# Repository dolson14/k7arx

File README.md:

# K7ARX Project Repository

A place to keep research and work on various electronics and radio projects.

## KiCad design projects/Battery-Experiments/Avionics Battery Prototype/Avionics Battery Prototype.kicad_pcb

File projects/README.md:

# Projects

Hardware, software, vaporware!

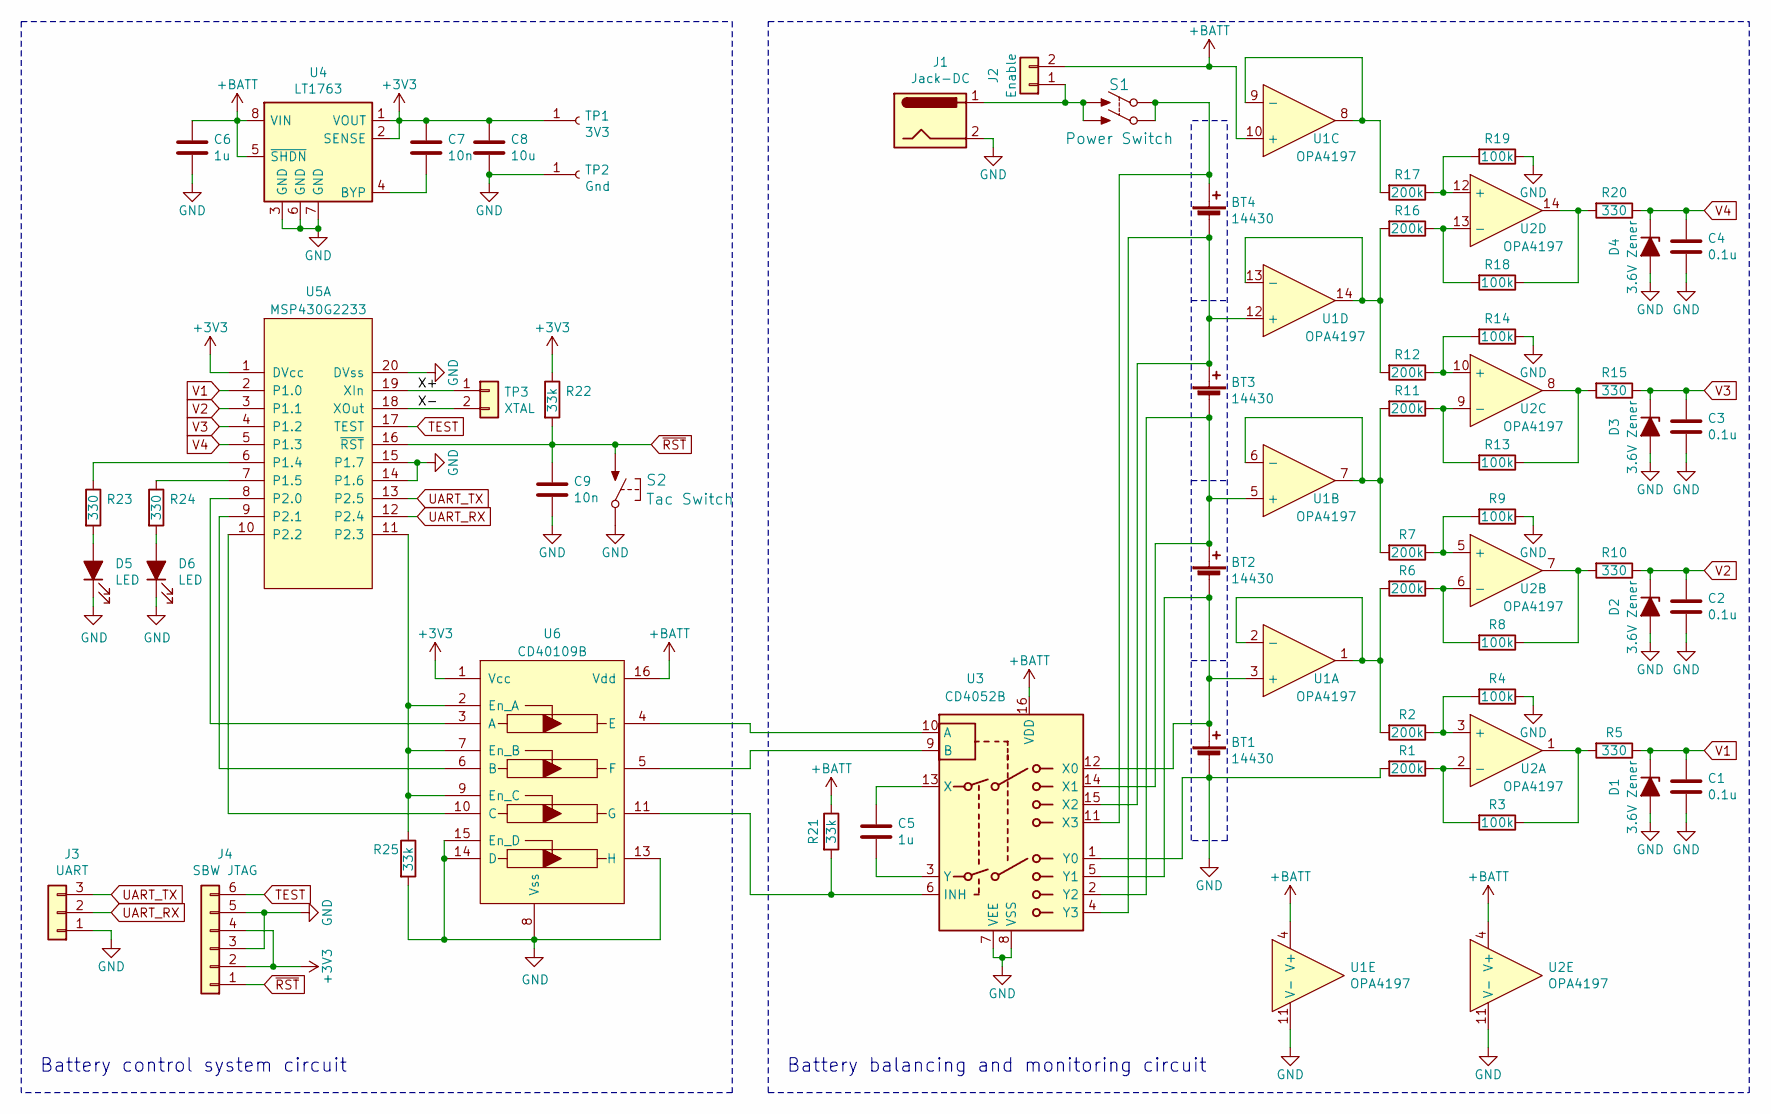
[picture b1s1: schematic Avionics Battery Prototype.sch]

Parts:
BT1, BT2, BT3, BT4: 14430; Keystone-92 Battery_Contact 14430
C1, C2, C3, C4: 0.1u; C_1206_HandSoldering
C5, C6: 1u; C_1206_HandSoldering
C7, C9: 10n; C_1206_HandSoldering
C8: 10u; C_1206_HandSoldering
D1, D2, D3, D4: 3.6V Zener; D_SOD-123F
D5, D6: LED; LED_1206_HandSoldering
J1: Jack-DC; Banana_Jack_2Pin
J2: Enable; Pin_Header_Straight_1x02_Pitch2.54mm
J3: UART; Pin_Header_Straight_1x03_Pitch2.54mm
J4: SBW JTAG; Tag-Connect_TC2030-NL
R1, R2, R6, R7, R11, R12, R16, R17: 200k; R_1206_HandSoldering
R3, R4, R8, R9, R13, R14, R18, R19: 100k; R_1206_HandSoldering
R5, R10, R15, R20, R23, R24: 330; R_1206_HandSoldering
R21, R22, R25: 33k; R_1206_HandSoldering
S1: Power Switch; PB400 DPST Pushbutton Switch
S2: Tac Switch; EVQ2_Momentary_Switch
TP1: 3V3; Pin_Header_Straight_1x01_Pitch2.54mm
TP2: Gnd; Pin_Header_Straight_1x01_Pitch2.54mm
TP3: XTAL; 8MM-11 2-pin PCB socket
U1, U2: OPA4197; SOIC-14_N
U3: CD4052B; SO-16-N
U4: LT1763; SOIC-8-N
U5: MSP430G2233; SSOP-20
U6: CD40109B; SO-16-N

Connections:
+3V3: C7.1, C8.1, J4.2, J4.4, R22.1, TP1.1, U4.1 (VOUT), U4.2 (SENSE), U5.1 (DVcc), U6.1 (Vcc)
+BATT: C6.1, J2.2, R21.1, U1.4 (V+), U1.10 (+), U2.4 (V+), U3.16 (VDD), U4.5 (~SHDN), U4.8 (VIN), U6.16 (Vdd)
/X+: TP3.1, U5.19 (XIn)
/X-: TP3.2, U5.18 (XOut)
GND: BT1.2 (-), C1.2, C2.2, C3.2, C4.2, C6.2, C8.2, C9.2, D1.2 (A), D2.2 (A), D3.2 (A), D4.2 (A), D5.1 (K), D6.1 (K), J1.2, J3.1, J4.3, J4.5, R1.2, R4.1, R9.1, R14.1, R19.1, R25.2, S2.2 (COM), TP2.1, U1.11 (V-), U2.11 (V-), U3.1 (Y0), U3.7 (VEE), U3.8 (VSS), U4.3 (GND), U4.6 (GND), U4.7 (GND), U5.14 (P1.6), U5.15 (P1.7), U5.20 (DVss), U6.8 (Vss), U6.13 (H), U6.14 (D), U6.15 (En_D)
unnamed: BT1.1 (+), BT2.2 (-), U1.3 (+), U3.5 (Y1), U3.12 (X0)
unnamed: BT2.1 (+), BT3.2 (-), U1.5 (+), U3.2 (Y2), U3.14 (X1)
unnamed: BT3.1 (+), BT4.2 (-), U1.12 (+), U3.4 (Y3), U3.15 (X2)
unnamed: BT4.1 (+), S1.2 (COM1), S1.4 (COM2), U3.11 (X3)
unnamed: C5.1, U3.13 (X)
unnamed: C5.2, U3.3 (Y)
unnamed: C7.2, U4.4 (BYP)
unnamed: D5.2 (A), R23.2
unnamed: D6.2 (A), R24.2
unnamed: J1.1, J2.1, S1.1 (NO1), S1.3 (NO2)
unnamed: R1.1, R3.2, U2.2 (-)
unnamed: R2.1, R4.2, U2.3 (+)
unnamed: R2.2, R6.2, U1.1, U1.2 (-)
unnamed: R3.1, R5.2, U2.1
unnamed: R6.1, R8.2, U2.6 (-)
unnamed: R7.1, R9.2, U2.5 (+)
unnamed: R8.1, R10.2, U2.7
unnamed: R11.1, R13.2, U2.9 (-)
unnamed: R7.2, R11.2, U1.6 (-), U1.7
unnamed: R12.1, R14.2, U2.10 (+)
unnamed: R12.2, R16.2, U1.13 (-), U1.14
unnamed: R13.1, R15.2, U2.8
unnamed: R16.1, R18.2, U2.13 (-)
unnamed: R17.1, R19.2, U2.12 (+)
unnamed: R17.2, U1.8, U1.9 (-)
unnamed: R18.1, R20.2, U2.14
unnamed: R21.2, U3.6 (INH), U6.11 (G)
unnamed: R23.1, U5.6 (P1.4)
unnamed: R24.1, U5.7 (P1.5)
unnamed: R25.1, U5.11 (P2.3), U6.2 (En_A), U6.7 (En_B), U6.9 (En_C)
unnamed: U3.9 (B), U6.5 (F)
unnamed: U3.10 (A), U6.4 (E)
unnamed: U5.8 (P2.0), U6.3 (A)
unnamed: U5.9 (P2.1), U6.6 (B)
unnamed: U5.10 (P2.2), U6.10 (C)
TEST: J4.6, U5.17 (TEST)
UART_RX: J3.2, U5.12 (P2.4)
UART_TX: J3.3, U5.13 (P2.5)
V1: C1.1, D1.1 (K), R5.1, U5.2 (P1.0)
V2: C2.1, D2.1 (K), R10.1, U5.3 (P1.1)
V3: C3.1, D3.1 (K), R15.1, U5.4 (P1.2)
V4: C4.1, D4.1 (K), R20.1, U5.5 (P1.3)
~RST: C9.1, J4.1, R22.2, S2.1 (NO), U5.16 (~RST)

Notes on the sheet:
Battery balancing and monitoring circuit
Battery control system circuit

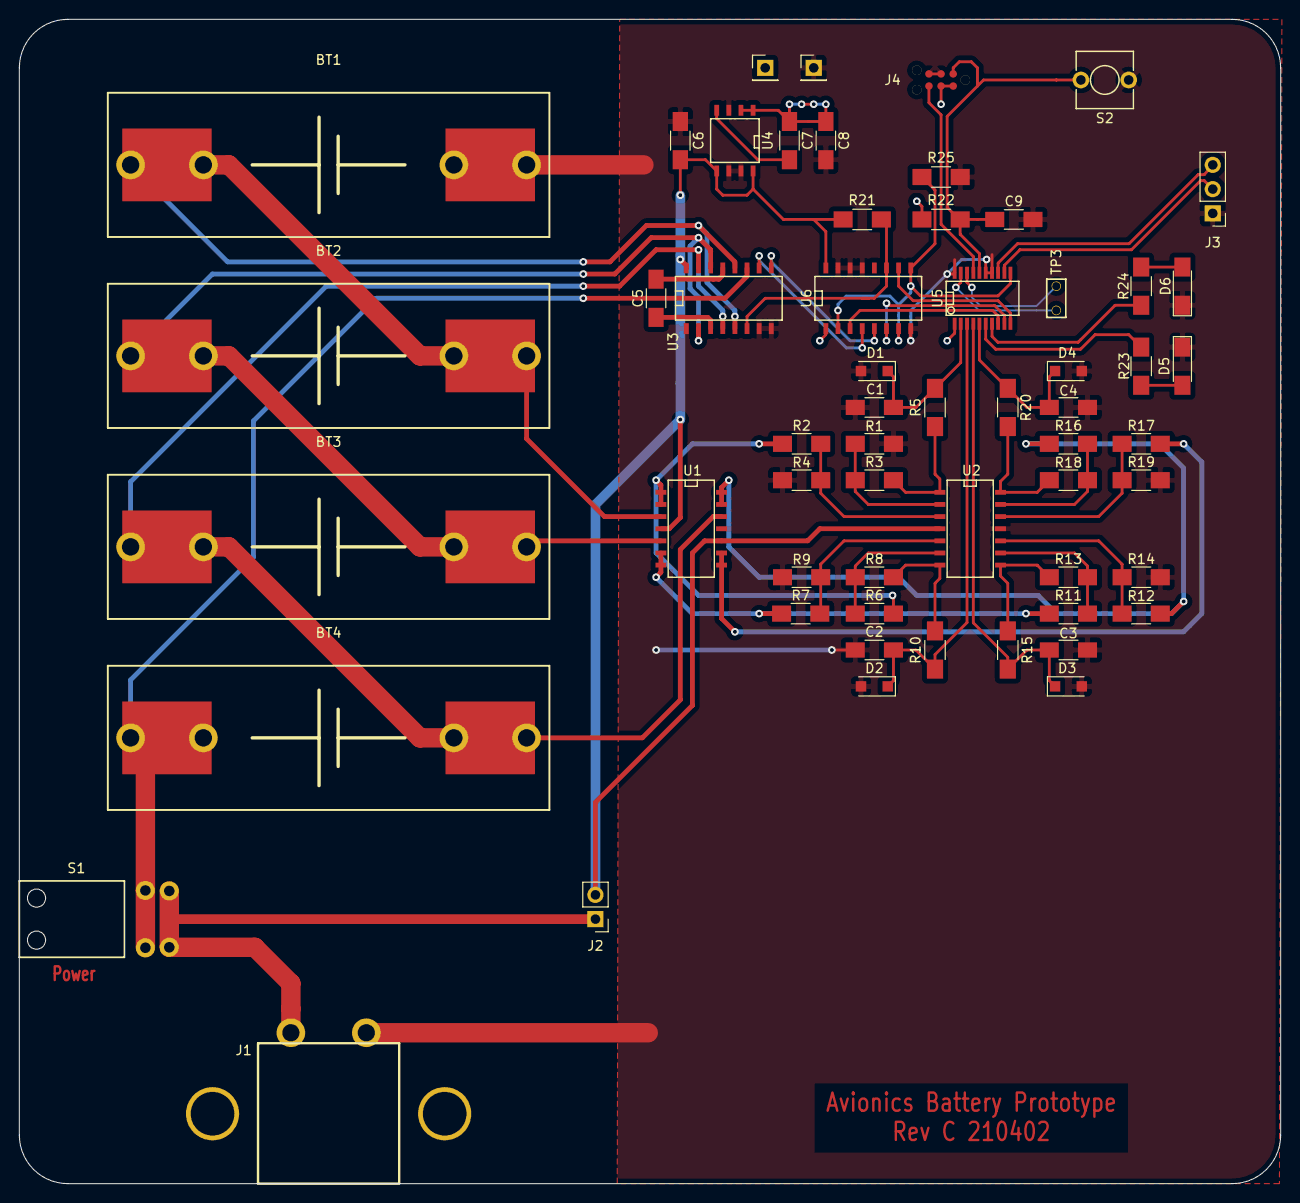
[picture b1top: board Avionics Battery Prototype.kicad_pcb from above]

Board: 2 copper layers, 132.1 x 121.9 mm, 59 parts (0 on the bottom side), 48 nets.

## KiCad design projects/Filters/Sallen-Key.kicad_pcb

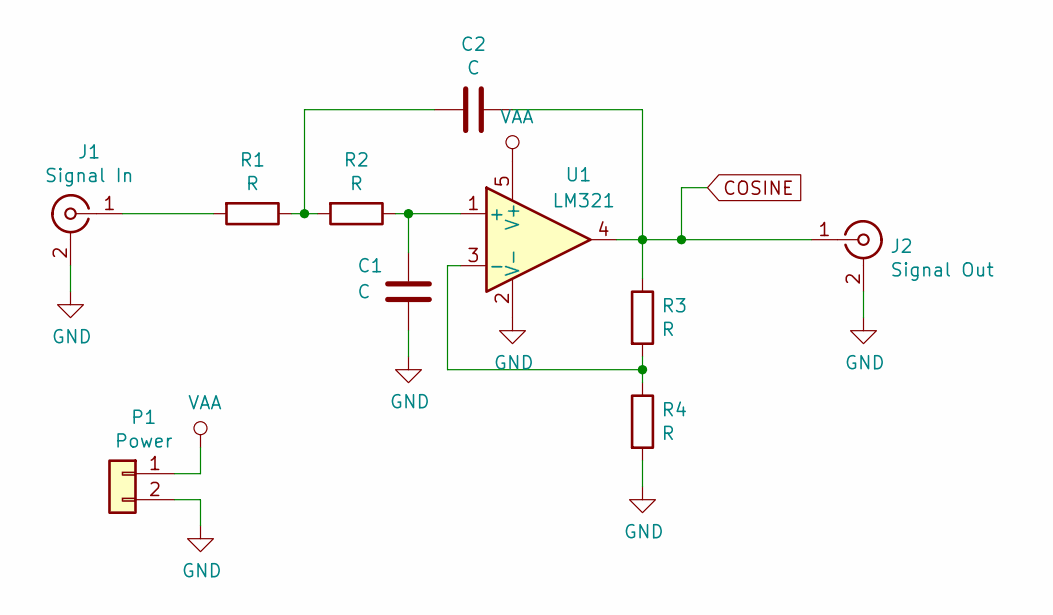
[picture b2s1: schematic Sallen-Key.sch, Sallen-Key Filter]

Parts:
C1, C2: C; C_0805_2012Metric_Pad1.15x1.40mm_HandSolder
J1: Signal In; SMA_Amphenol_132289_EdgeMount
J2: Signal Out; SMA_Amphenol_132289_EdgeMount
P1: Power; EP_3.96-pin_1x2
R1, R2, R3, R4: R; R_0805_2012Metric_Pad1.15x1.40mm_HandSolder
U1: LM321; SOT-23-5

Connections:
COSINE: C2.1, J2.1 (In), R3.1, U1.4
GND: C1.2, J1.2 (Ext), J2.2 (Ext), P1.2, R4.2, U1.2 (V-)
unnamed: C1.1, R2.1, U1.1 (+)
unnamed: C2.2, R1.1, R2.2
unnamed: J1.1 (In), R1.2
unnamed: R3.2, R4.1, U1.3 (-)
VAA: P1.1, U1.5 (V+)

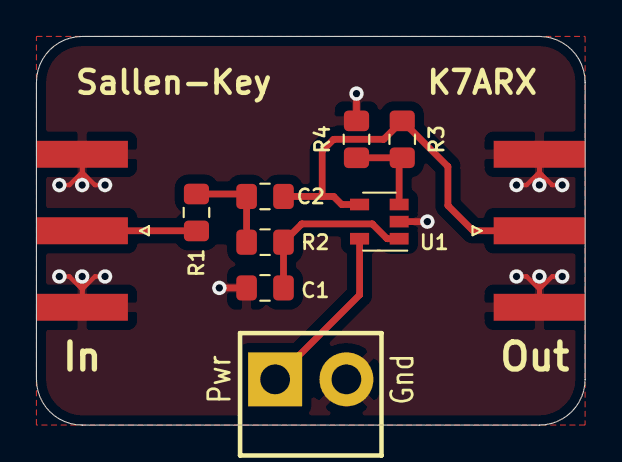
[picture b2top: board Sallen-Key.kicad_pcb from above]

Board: 2 copper layers, 30.5 x 21.6 mm, 10 parts (0 on the bottom side), 7 nets.

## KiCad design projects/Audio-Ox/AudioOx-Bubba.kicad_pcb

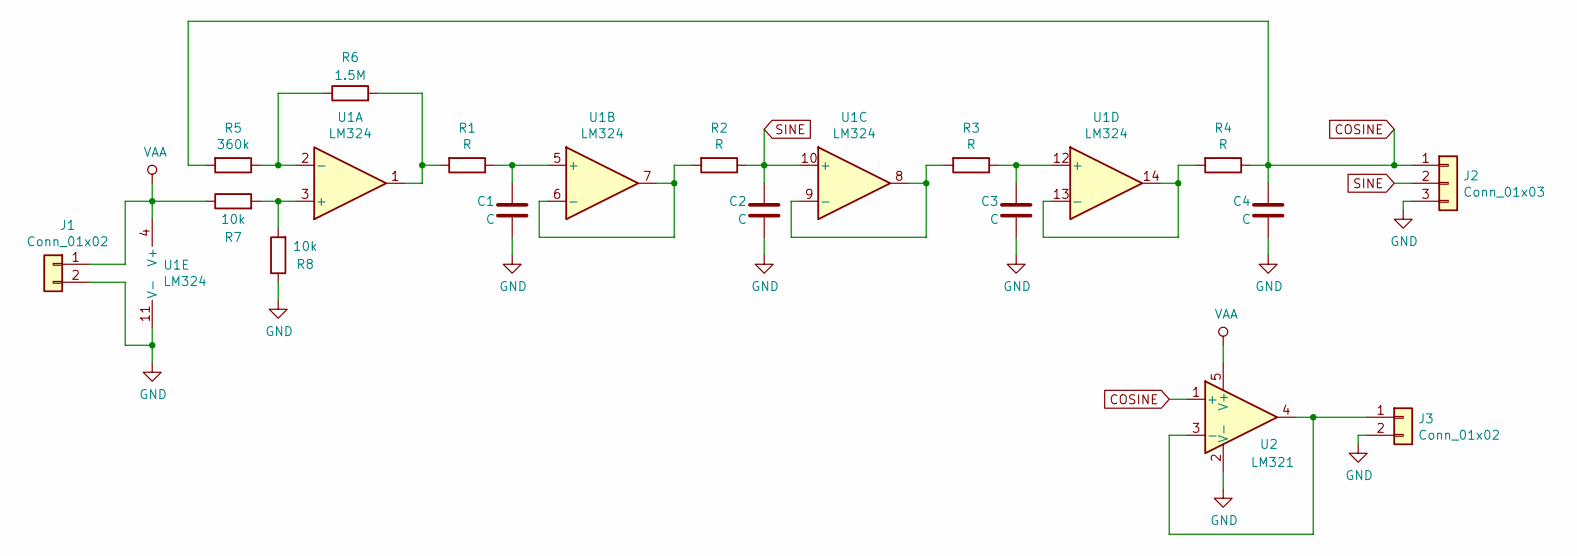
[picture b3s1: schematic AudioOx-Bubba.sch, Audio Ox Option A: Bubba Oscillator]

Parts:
C1, C2, C3, C4: C; C_0805_2012Metric_Pad1.15x1.40mm_HandSolder
J1, J3: Conn_01x02; PinHeader_1x02_P2.54mm_Vertical
J2: Conn_01x03; PinHeader_1x03_P2.54mm_Vertical
R1, R2, R3, R4: R; R_0805_2012Metric_Pad1.15x1.40mm_HandSolder
R5: 360k; R_0805_2012Metric_Pad1.15x1.40mm_HandSolder
R6: 1.5M; R_0805_2012Metric_Pad1.15x1.40mm_HandSolder
R7, R8: 10k; R_0805_2012Metric_Pad1.15x1.40mm_HandSolder
U1: LM324; SOIC-14_3.9x8.7mm_P1.27mm
U2: LM321; SOT-23-5

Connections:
COSINE: C4.1, J2.1, R4.1, R5.2, U2.1 (+)
GND: C1.2, C2.2, C3.2, C4.2, J1.2, J2.3, J3.2, R8.1, U1.11 (V-), U2.2 (V-)
unnamed: C1.1, R1.1, U1.5 (+)
unnamed: C3.1, R3.1, U1.12 (+)
unnamed: J3.1, U2.3 (-), U2.4
unnamed: R1.2, R6.2, U1.1
unnamed: R2.2, U1.6 (-), U1.7
unnamed: R3.2, U1.8, U1.9 (-)
unnamed: R4.2, U1.13 (-), U1.14
unnamed: R5.1, R6.1, U1.2 (-)
unnamed: R7.2, R8.2, U1.3 (+)
SINE: C2.1, J2.2, R2.1, U1.10 (+)
VAA: J1.1, R7.1, U1.4 (V+), U2.5 (V+)

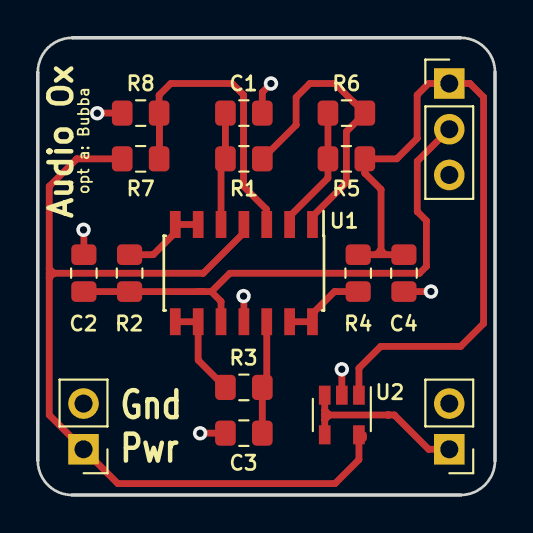
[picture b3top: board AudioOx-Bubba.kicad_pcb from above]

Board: 2 copper layers, 25.4 x 25.4 mm, 17 parts (0 on the bottom side), 13 nets.

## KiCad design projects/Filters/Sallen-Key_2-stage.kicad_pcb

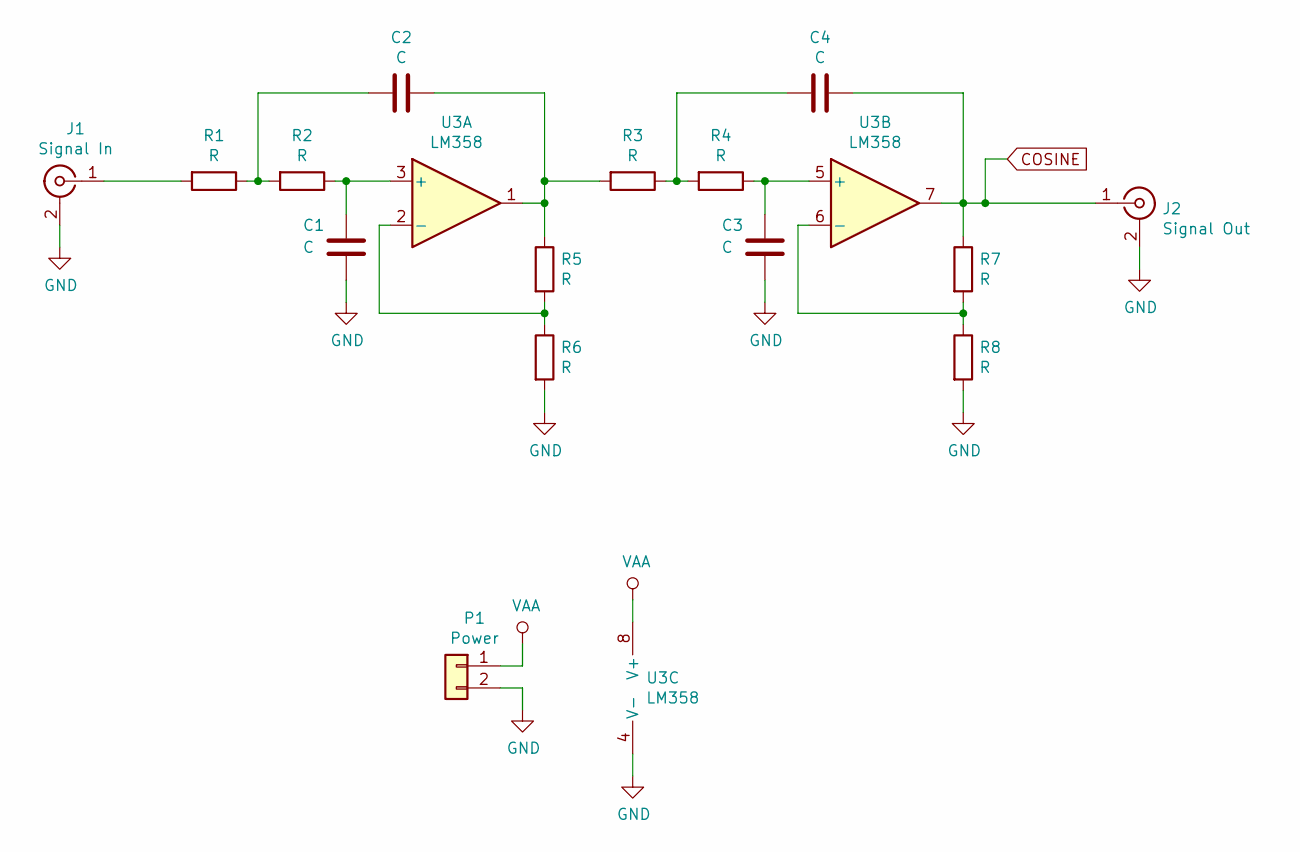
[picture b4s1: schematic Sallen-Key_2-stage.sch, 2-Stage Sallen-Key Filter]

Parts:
C1, C2, C3, C4: C; C_0805_2012Metric_Pad1.15x1.40mm_HandSolder
J1: Signal In; SMA_Amphenol_132289_EdgeMount
J2: Signal Out; SMA_Amphenol_132289_EdgeMount
P1: Power; EP_3.96-pin_1x2
R1, R2, R3, R4, R5, R6, R7, R8: R; R_0805_2012Metric_Pad1.15x1.40mm_HandSolder
U3: LM358; SOIC-8_3.9x4.9mm_P1.27mm

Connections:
COSINE: C4.1, J2.1 (In), R7.1, U3.7
GND: C1.2, C3.2, J1.2 (Ext), J2.2 (Ext), P1.2, R6.2, R8.2, U3.4 (V-)
unnamed: C1.1, R2.1, U3.3 (+)
unnamed: C2.1, R3.2, R5.1, U3.1
unnamed: C2.2, R1.1, R2.2
unnamed: C3.1, R4.1, U3.5 (+)
unnamed: C4.2, R3.1, R4.2
unnamed: J1.1 (In), R1.2
unnamed: R5.2, R6.1, U3.2 (-)
unnamed: R7.2, R8.1, U3.6 (-)
VAA: P1.1, U3.8 (V+)

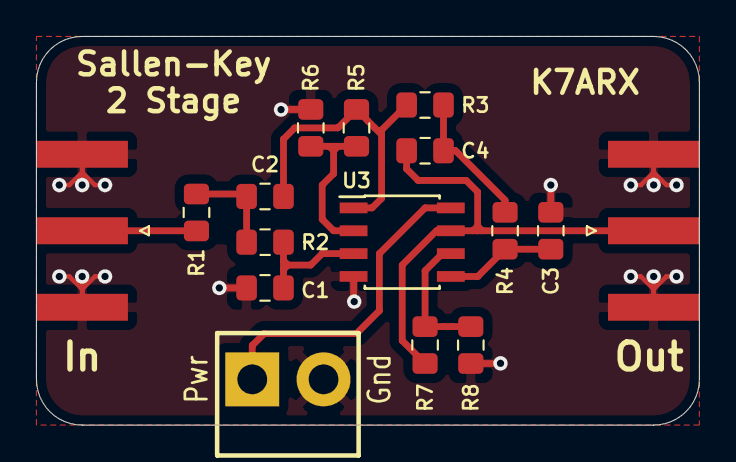
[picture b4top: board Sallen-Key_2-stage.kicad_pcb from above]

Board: 2 copper layers, 36.8 x 21.6 mm, 16 parts (0 on the bottom side), 11 nets.

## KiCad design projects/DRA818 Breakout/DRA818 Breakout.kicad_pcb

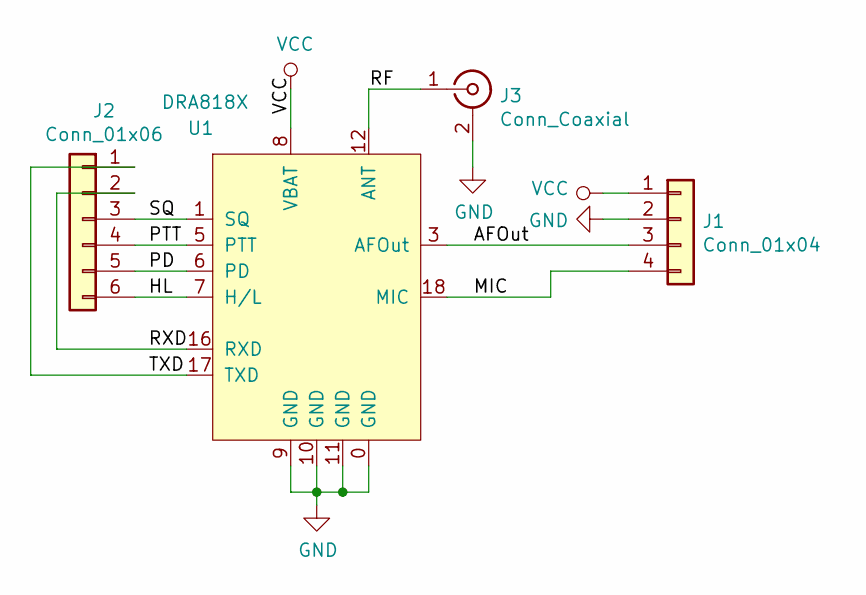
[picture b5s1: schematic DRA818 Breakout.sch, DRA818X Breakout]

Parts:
J1: Conn_01x04; PinHeader_1x04_P2.54mm_Vertical
J2: Conn_01x06; PinHeader_1x06_P2.54mm_Vertical
J3: Conn_Coaxial; SMA_Board_Edge
U1: DRA818X; DRA818

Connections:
/AFOut: J1.3, U1.3 (AFOut)
/HL: J2.6, U1.7 (H/L)
/MIC: J1.4, U1.18 (MIC)
/PD: J2.5, U1.6 (PD)
/PTT: J2.4, U1.5 (PTT)
/RF: J3.1 (In), U1.12 (ANT)
/RXD: J2.2, U1.16 (RXD)
/SQ: J2.3, U1.1 (SQ)
/TXD: J2.1, U1.17 (TXD)
GND: J1.2, J3.2 (Ext), U1.0 (GND), U1.9 (GND), U1.10 (GND), U1.11 (GND)
VCC: J1.1, U1.8 (VBAT)

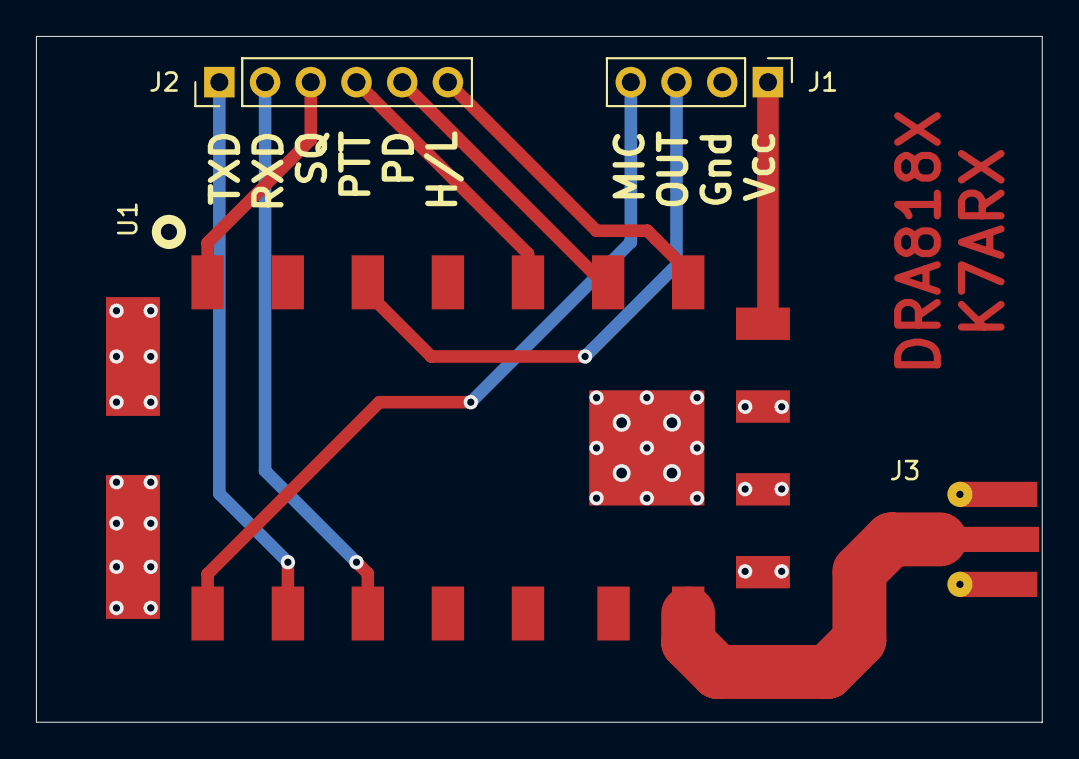
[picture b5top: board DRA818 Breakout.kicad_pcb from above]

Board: 2 copper layers, 55.9 x 38.1 mm, 4 parts (0 on the bottom side), 11 nets.

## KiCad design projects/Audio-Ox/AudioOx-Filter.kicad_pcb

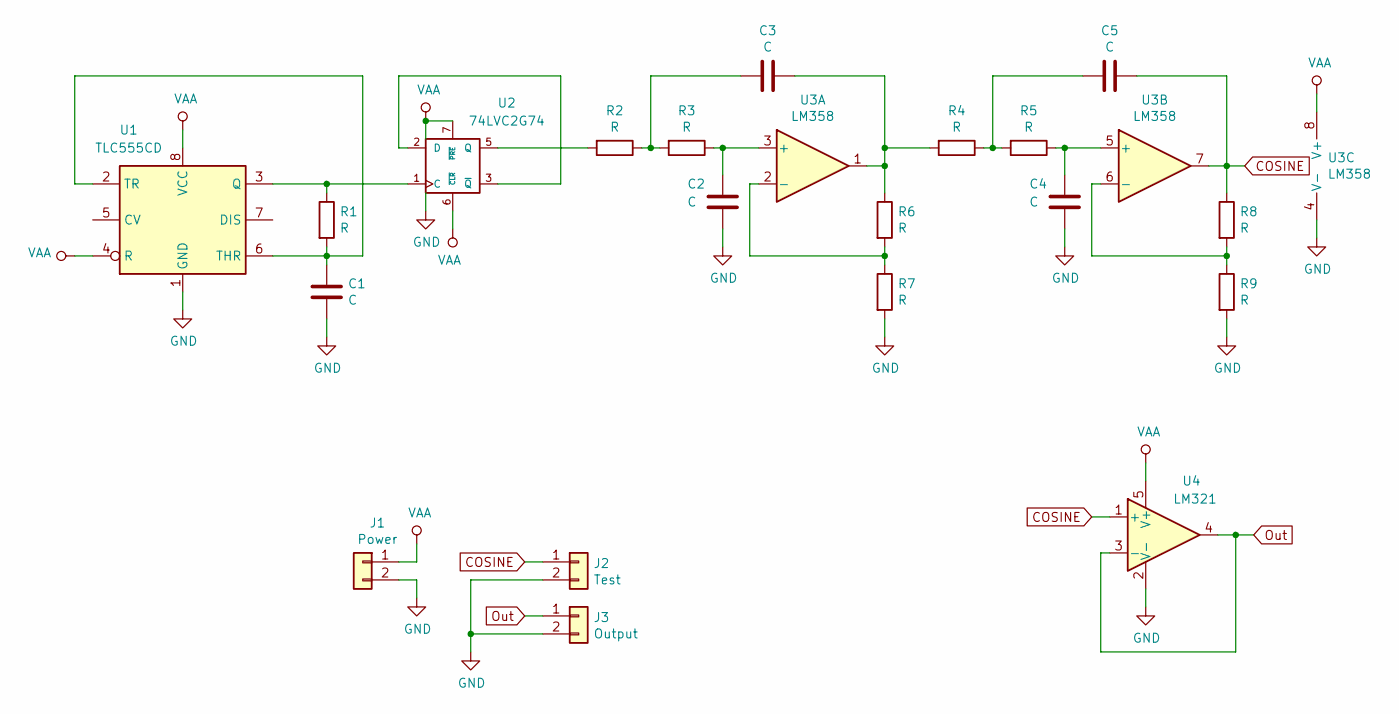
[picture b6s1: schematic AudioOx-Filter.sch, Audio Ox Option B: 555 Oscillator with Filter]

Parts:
C1, C2, C3, C4, C5: C; C_0805_2012Metric_Pad1.15x1.40mm_HandSolder
J1: Power; PinHeader_1x02_P2.54mm_Vertical
J2: Test; PinHeader_1x02_P2.54mm_Vertical
J3: Output; PinHeader_1x02_P2.54mm_Vertical
R1, R2, R3, R4, R5, R6, R7, R8, R9: R; R_0805_2012Metric_Pad1.15x1.40mm_HandSolder
U1: TLC555CD; SOIC-8_3.9x4.9mm_P1.27mm
U2: 74LVC2G74; MSOP-8_3x3mm_P0.65mm
U3: LM358; SOIC-8_3.9x4.9mm_P1.27mm
U4: LM321; SOT-23-5

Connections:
COSINE: C5.1, J2.1, R8.1, U3.7, U4.1 (+)
GND: C1.2, C2.2, C4.2, J1.2, J2.2, J3.2, R7.2, R9.2, U1.1 (GND), U2.4 (GND), U3.4 (V-), U4.2 (V-)
unnamed: C1.1, R1.2, U1.2 (TR), U1.6 (THR)
unnamed: C2.1, R3.1, U3.3 (+)
unnamed: C3.1, R4.2, R6.1, U3.1
unnamed: C3.2, R2.1, R3.2
unnamed: C4.1, R5.1, U3.5 (+)
unnamed: C5.2, R4.1, R5.2
unnamed: R1.1, U1.3 (Q), U2.1 (C)
unnamed: R2.2, U2.5 (Q)
unnamed: R6.2, R7.1, U3.2 (-)
unnamed: R8.2, R9.1, U3.6 (-)
unnamed: U2.2 (D), U2.3 (~Q)
Out: J3.1, U4.3 (-), U4.4
VAA: J1.1, U1.4 (R), U1.8 (VCC), U2.6 (~CLR), U2.7 (~PRE), U2.8 (VCC), U3.8 (V+), U4.5 (V+)

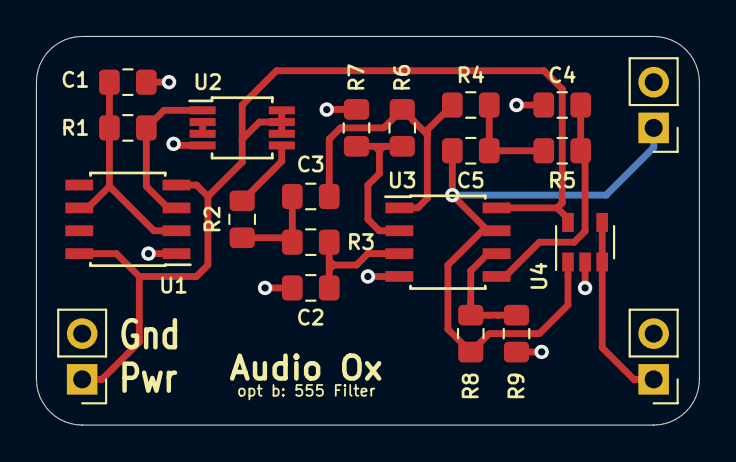
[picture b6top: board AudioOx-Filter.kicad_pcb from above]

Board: 2 copper layers, 36.8 x 21.6 mm, 21 parts (0 on the bottom side), 15 nets.

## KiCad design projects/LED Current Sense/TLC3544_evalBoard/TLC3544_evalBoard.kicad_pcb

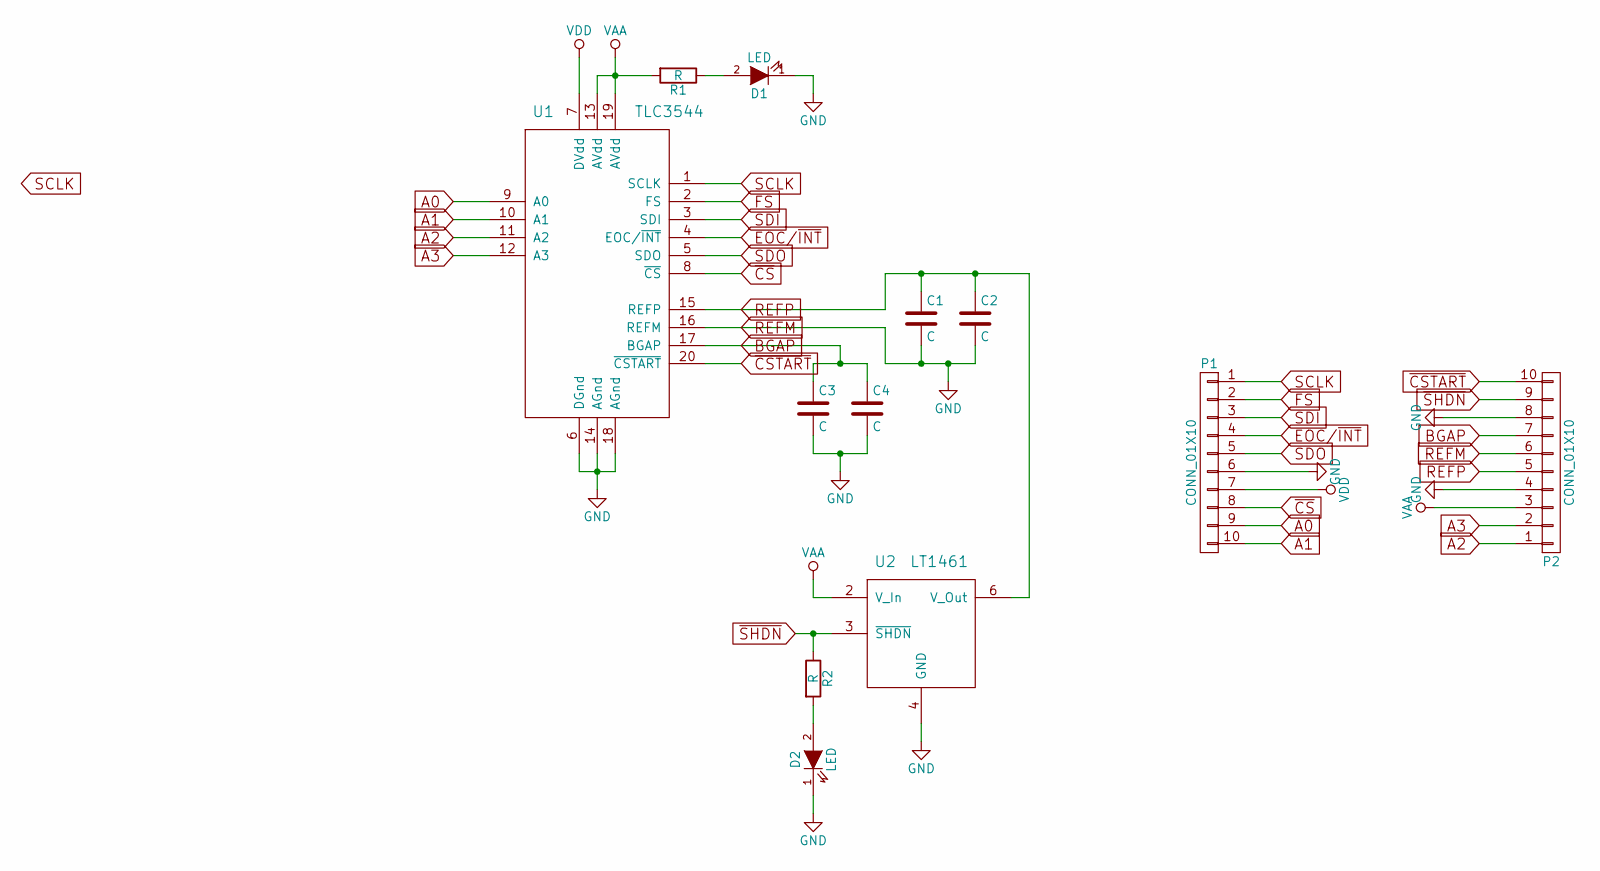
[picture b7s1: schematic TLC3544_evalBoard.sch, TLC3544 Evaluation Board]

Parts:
C1, C2, C3, C4: C; C_1206_HandSoldering
D1, D2: LED; LED-0805
P1, P2: CONN_01X10; Socket_Strip_Straight_1x10
R1, R2: R; R_0805_HandSoldering
U1: TLC3544; SOIC-20
U2: LT1461; SOIC-8-N

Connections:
A0: P1.9, U1.9 (A0)
A1: P1.10, U1.10 (A1)
A2: P2.1, U1.11 (A2)
A3: P2.2, U1.12 (A3)
BGAP: C3.1, C4.1, P2.7, U1.17 (BGAP)
EOC/~INT: P1.4, U1.4 (EOC/~INT)
FS: P1.2, U1.2 (FS)
unnamed: D1.2 (A), R1.1
unnamed: D2.2 (A), R2.2
REFM: C1.2, C2.2, C3.2, C4.2, D1.1 (K), D2.1 (K), P1.6, P2.4, P2.6, P2.8, U1.6 (DGnd), U1.14 (AGnd), U1.16 (REFM), U1.18 (AGnd), U2.4 (GND)
REFP: C1.1, C2.1, P2.5, U1.15 (REFP), U2.6 (V_Out)
SCLK: P1.1, U1.1 (SCLK)
SDI: P1.3, U1.3 (SDI)
SDO: P1.5, U1.5 (SDO)
VAA: P2.3, R1.2, U1.13 (AVdd), U1.19 (AVdd), U2.2 (V_In)
VDD: P1.7, U1.7 (DVdd)
~CS: P1.8, U1.8 (~CS)
~CSTART: P2.10, U1.20 (~CSTART)
~SHDN: P2.9, R2.1, U2.3 (~SHDN)

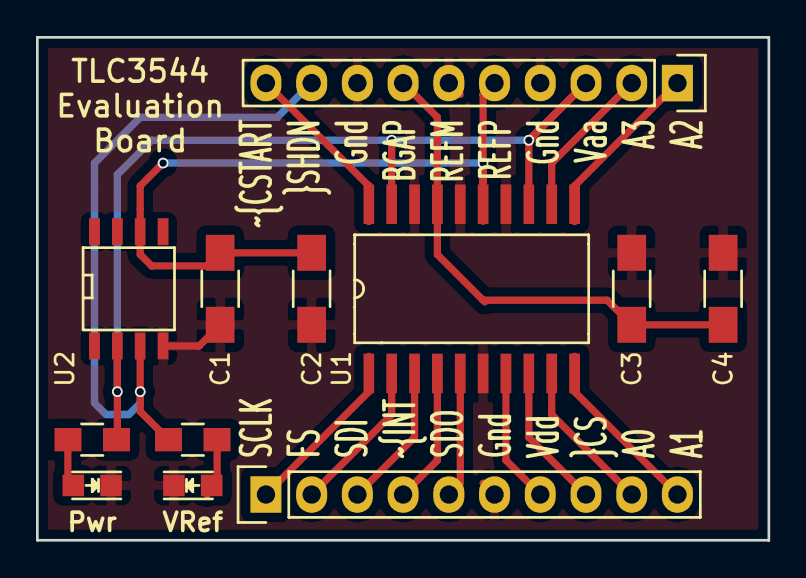
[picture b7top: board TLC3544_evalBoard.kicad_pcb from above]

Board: 2 copper layers, 40.6 x 27.9 mm, 12 parts (0 on the bottom side), 19 nets.

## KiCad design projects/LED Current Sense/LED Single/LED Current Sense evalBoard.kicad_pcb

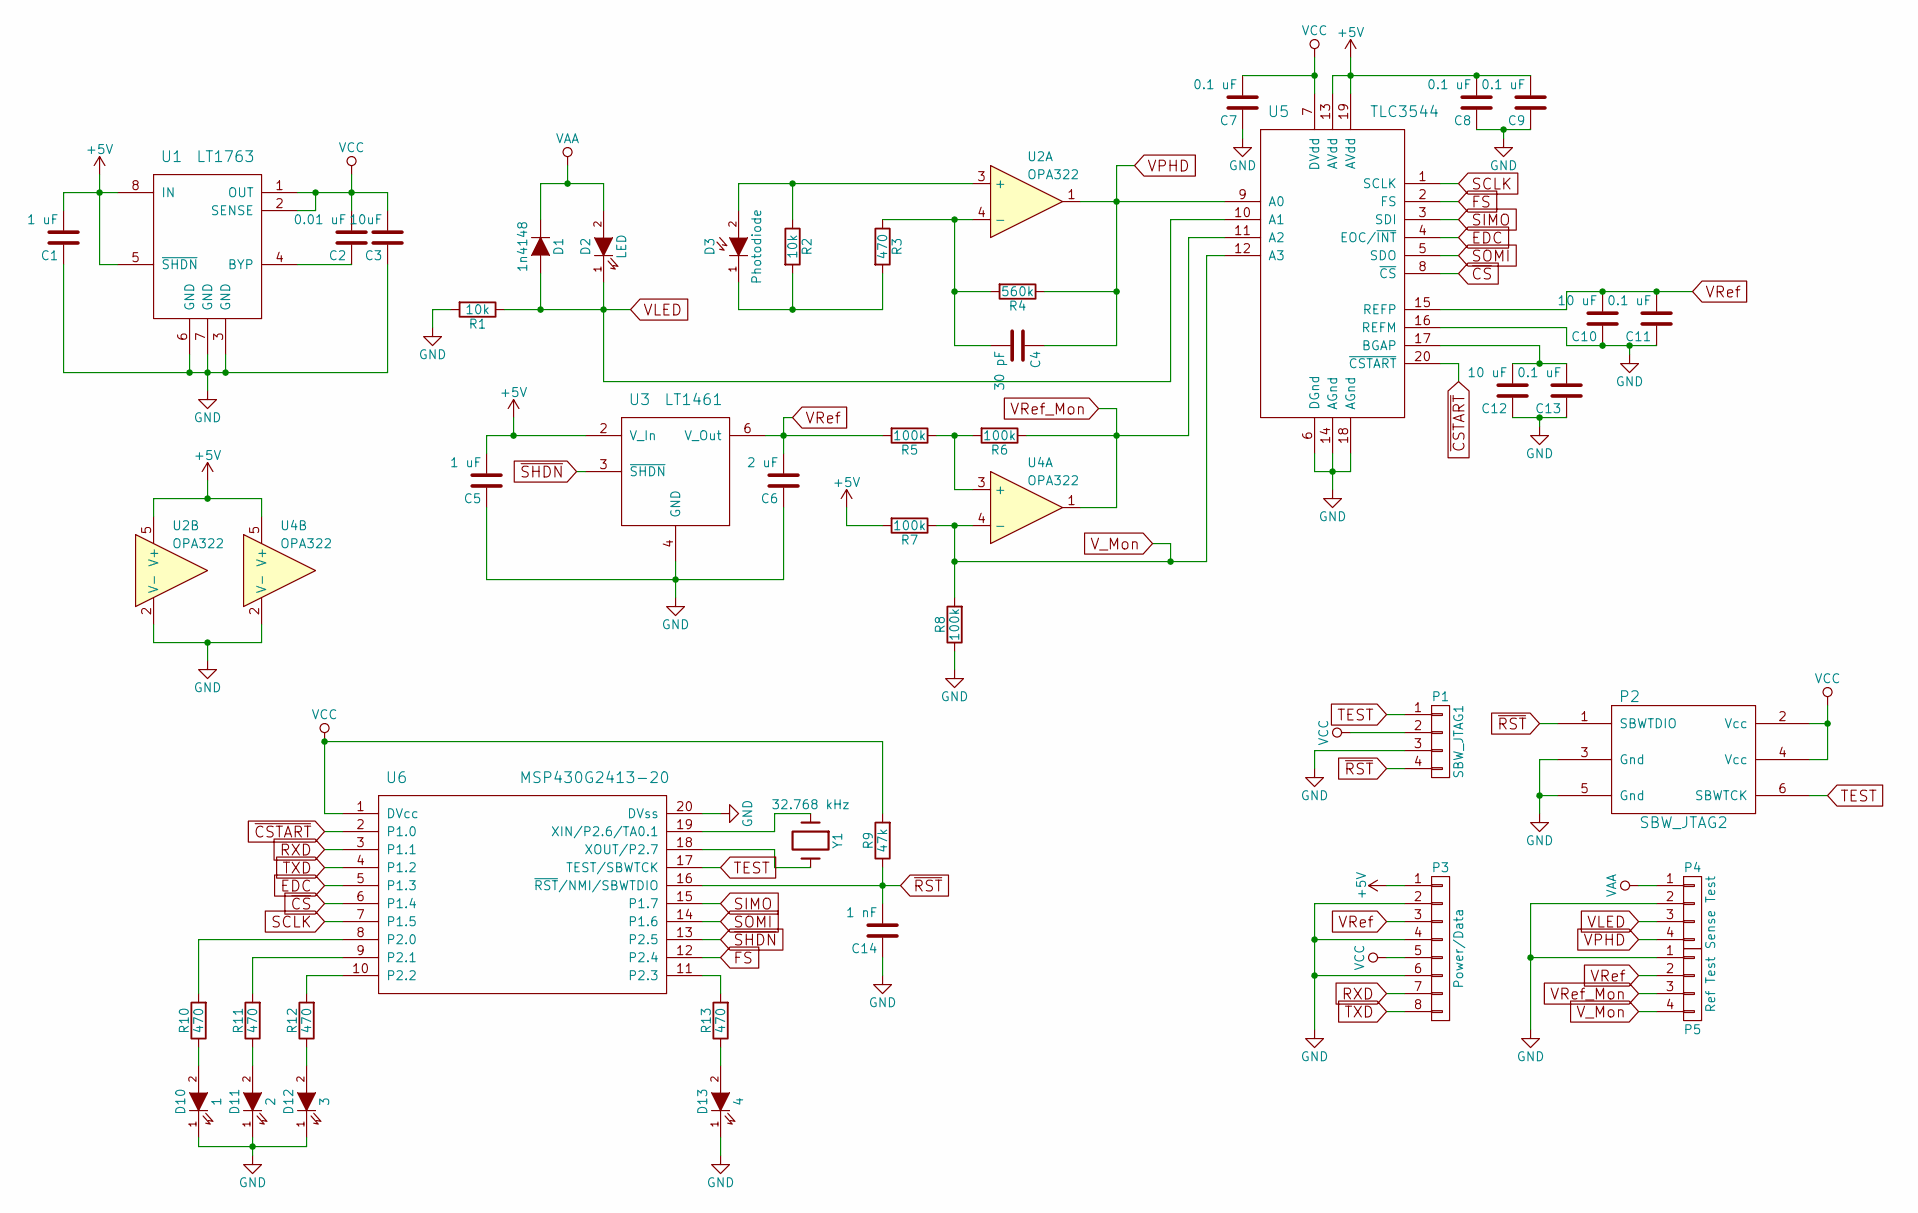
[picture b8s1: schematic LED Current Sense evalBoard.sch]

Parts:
C1, C5: 1 uF; C_1206_HandSoldering
C2: 0.01 uF; C_1206_HandSoldering
C3: 10uF; C_1206_HandSoldering
C4: 30 pF; C_1206_HandSoldering
C6: 2 uF; C_1206_HandSoldering
C7, C8, C9, C11, C13: 0.1 uF; C_1206_HandSoldering
C10, C12: 10 uF; C_1206_HandSoldering
C14: 1 nF; C_1206_HandSoldering
D1: 1n4148; Diode_DO-35_SOD27_Horizontal_RM10
D2: LED; LED-5MM
D3: Photodiode; LED-5MM
D10: 1; LED-0805
D11: 2; LED-0805
D12: 3; LED-0805
D13: 4; LED-0805
P1: SBW_JTAG1; Pin_Header_Straight_1x04
P2: SBW_JTAG2; Tag-Connect_TC2030
P3: Power/Data; Pin_Header_Straight_1x08
P4: Sense Test; Pin_Header_Straight_1x04
P5: Ref Test; Pin_Header_Straight_1x04
R1, R2: 10k; Resistor_Horizontal_RM10mm
R3: 470; Resistor_Horizontal_RM10mm
R4: 560k; Resistor_Horizontal_RM10mm
R5, R6, R7, R8: 100k; R_1206_HandSoldering
R9: 47k; R_1206_HandSoldering
R10, R11, R12, R13: 470; R_1206_HandSoldering
U1: LT1763; SOIC-8-N
U2, U4: OPA322; SOT-23-5
U3: LT1461; SOIC-8-N
U5: TLC3544; SOIC-20
U6: MSP430G2413-20; SSOP-20
Y1: 32.768 kHz; Crystal_Round_Horizontal_2mm

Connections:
+5V: C1.2, C5.2, C8.2, C9.2, P3.1, R7.2, U1.5 (~SHDN), U1.8 (IN), U2.5 (V+), U3.2 (V_In), U4.5 (V+), U5.13 (AVdd), U5.19 (AVdd)
EDC: U5.4 (EOC/~INT), U6.5 (P1.3)
FS: U5.2 (FS), U6.12 (P2.4)
GND: C1.1, C3.1, C5.1, C6.1, C7.1, C8.1, C9.1, C10.1, C11.1, C12.1, C13.1, C14.1, D10.1 (K), D11.1 (K), D12.1 (K), D13.1 (K), P1.3, P2.3 (Gnd), P2.5 (Gnd), P3.2, P3.4, P3.6, P4.2, P5.1, R1.2, R8.1, U1.3 (GND), U1.6 (GND), U1.7 (GND), U2.2 (V-), U3.4 (GND), U4.2 (V-), U5.6 (DGnd), U5.14 (AGnd), U5.16 (REFM), U5.18 (AGnd), U6.20 (DVss)
unnamed: C2.1, U1.4 (BYP)
unnamed: C4.2, R3.1, R4.2, U2.4 (-)
unnamed: C12.2, C13.2, U5.17 (BGAP)
unnamed: D3.1 (K), R2.2, R3.2
unnamed: D3.2 (A), R2.1, U2.3 (+)
unnamed: D10.2 (A), R10.1
unnamed: D11.2 (A), R11.1
unnamed: D12.2 (A), R12.1
unnamed: D13.2 (A), R13.1
unnamed: R5.1, R6.2, U4.3 (+)
unnamed: R10.2, U6.8 (P2.0)
unnamed: R11.2, U6.9 (P2.1)
unnamed: R12.2, U6.10 (P2.2)
unnamed: R13.2, U6.11 (P2.3)
unnamed: U6.18 (XOUT/P2.7), Y1.2
unnamed: U6.19 (XIN/P2.6/TA0.1), Y1.1
RXD: P3.7, U6.3 (P1.1)
SCLK: U5.1 (SCLK), U6.7 (P1.5)
SIMO: U5.3 (SDI), U6.15 (P1.7)
SOMI: U5.5 (SDO), U6.14 (P1.6)
TEST: P1.1, P2.6 (SBWTCK), U6.17 (TEST/SBWTCK)
TXD: P3.8, U6.4 (P1.2)
VAA: D1.1 (K), D2.2 (A), P4.1
VCC: C2.2, C3.2, C7.2, P1.2, P2.2 (Vcc), P2.4 (Vcc), P3.5, R9.2, U1.1 (OUT), U1.2 (SENSE), U5.7 (DVdd), U6.1 (DVcc)
VLED: D1.2 (A), D2.1 (K), P4.3, R1.1, U5.10 (A1)
VPHD: C4.1, P4.4, R4.1, U2.1, U5.9 (A0)
VRef: C6.2, C10.2, C11.2, P3.3, P5.2, R5.2, U3.6 (V_Out), U5.15 (REFP)
VRef_Mon: P5.3, R6.1, U4.1, U5.11 (A2)
V_Mon: P5.4, R7.1, R8.2, U4.4 (-), U5.12 (A3)
~CS: U5.8 (~CS), U6.6 (P1.4)
~CSTART: U5.20 (~CSTART), U6.2 (P1.0)
~RST: C14.2, P1.4, P2.1 (SBWTDIO), R9.1, U6.16 (~RST~/NMI/SBWTDIO)
~SHDN: U3.3 (~SHDN), U6.13 (P2.5)

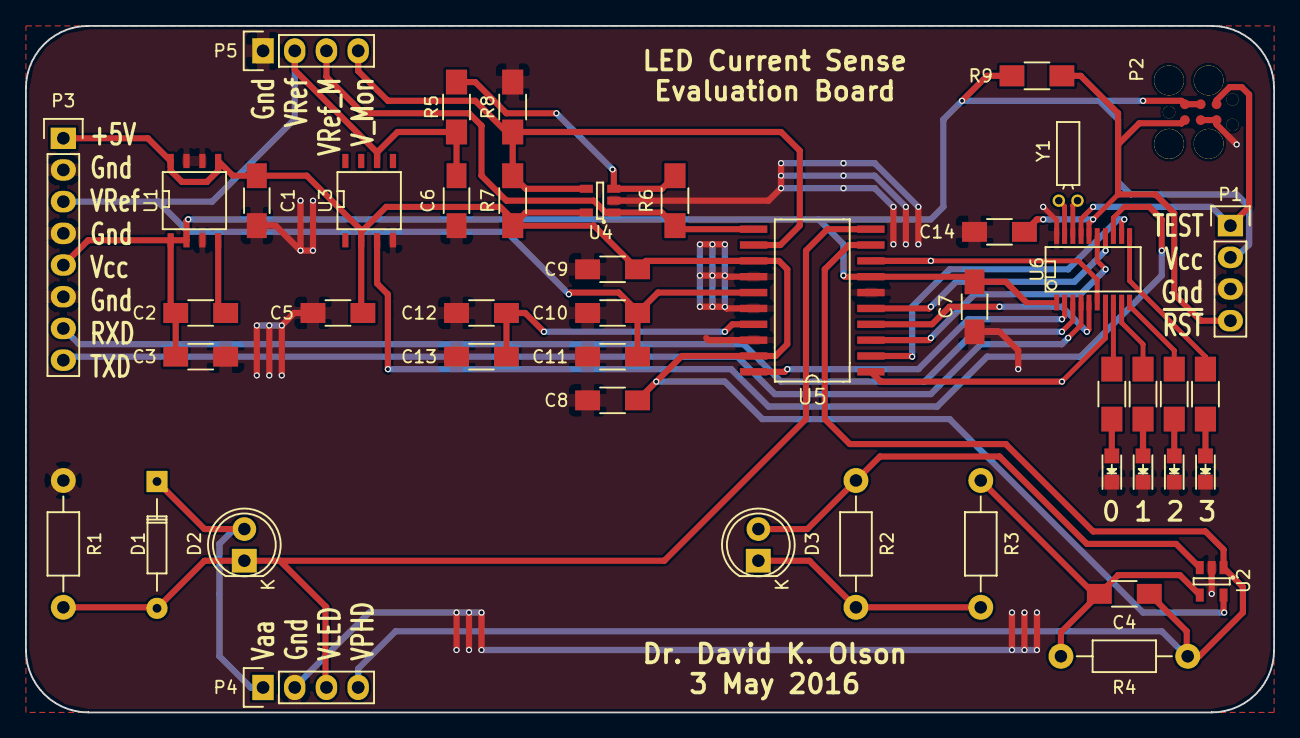
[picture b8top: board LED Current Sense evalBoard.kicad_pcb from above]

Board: 2 copper layers, 100.0 x 55.0 mm, 46 parts (0 on the bottom side), 37 nets.

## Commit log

2016-10-27 Initial Commit 161027
    Add initial directory structure
    Add various useful datasheets
    Add collected reference and application notes
2016-10-27 161027b
2016-10-27 161027c
2016-11-01 161101 Update A
2016-11-02 161102 Update A
    Adding initial KiCad files, including a simple project.
2016-11-03 20161103 Update A
2016-11-04 Inventory Database
    Added a mongodb database for keeping track of part inventory.
2016-11-23 161122 Update
2017-03-07 170307 Update
2017-03-10 170310 Update
2017-03-13 170313 Update
2017-03-29 170329 Update
2017-04-03 PyVISA Initiation
2017-04-03 PyVISA Initiation Again
2017-04-10 170410 Update
2017-04-10 170410b Update
2017-04-27 170427 Update
2017-05-25 Add Si5351 Register Map
2017-06-30 170630 Update
2017-09-07 170907 Update
2017-09-07 170907b Update
2017-09-08 170908 Update
2017-09-08 170908c Update
2017-09-18 170918 Update
2017-09-18 170918b Update
2017-10-02 171002 Update
2017-10-02 171002b Update
2017-10-05 171005 Update
2018-04-16 LT-AN45 Addition to collection
2018-04-16 LT3092 Addition
2018-04-17 NPP-301 Addition
2018-04-19 QFH Antennas and other
2018-04-20 Start of Launch Controller Project
2018-04-21 k7arx Stencils
2018-04-21 SBW Programmer Init
2018-05-02 Playing with .pro syntax
2018-05-04 Launch Controller Datasheets
2018-05-04 Kicad Generalized lib directories
2018-05-04 Clean up kicad libs
2018-05-14 Adding ARX Design Folder
2018-06-14 Add template
2018-06-19 Rearranging some misplaced files
2018-06-19 Remove old inventory
2018-06-19 Begin projects specifically oriented to radios. - Contribute file with specific dimensions to fix footprint for SMA connectors.
2018-06-19 Doc on model rocket payload bay
2018-06-20 Crystal Radio work
2018-06-21 MiniCircuits DataSheets
2019-02-14 Upload datasheet LTC4150
2019-02-14 Upload FR MSP430 variants datasheets
2019-02-28 updated datasheets and beginning of battery project
2019-10-10 Update 191010
2019-10-18 Start of DRA818
2021-03-05 Update for 2021 projects start
2021-03-05 Syncing Gwydion for 2021 projects start
2021-03-05 Taran sync for 2021 projects start
2021-03-10 AVB Start
2021-03-10 AVB Rev B Complete
2021-03-10 AVB add Xtal tp to uc
2021-03-11 Add Xtal plug project
2021-03-12 Syncing AVB Rev C
2021-03-12 Syncing AVB Rev C from Taran
2021-03-13 AVB Rev C Final
2021-03-17 Resync for Taran
2021-04-13 AVB Rev C and XTAL Plug Final
